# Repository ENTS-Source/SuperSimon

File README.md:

# ENTS "Simon Says" game

A two player version of the popular Simon Says game, with a fifth button.

## Pi Zero (2W) setup

1. Install Raspbian per normal
2. Enable SSH and WiFi to make configuration/development easier
3. `sudo apt update`
4. `sudo apt upgrade`
5. `sudo apt install python3-pgzero` (should already be installed)
6. Turn volume up on the Raspberry Pi and output device (speakers/monitor)
7. `git clone https://github.com/ENTS-Source/SuperSimon.git`
8. `cd SuperSimon`
9. `pgzrun simon.py` (to verify it works)

## Credits

Audio files are generated by ChatGPT under CC0 1.0

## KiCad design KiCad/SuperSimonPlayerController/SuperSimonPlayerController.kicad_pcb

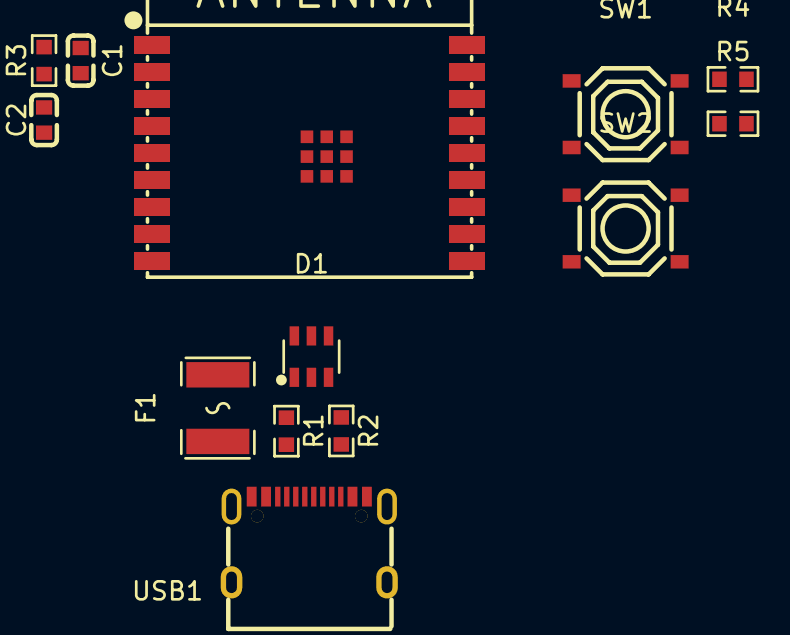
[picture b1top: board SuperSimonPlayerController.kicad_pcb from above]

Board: 2 copper layers, 13 parts (0 on the bottom side), 13 nets, no tracks yet.

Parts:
C1, C2: CL10A226MQ8NRNC; C0603
D1: USBLC6-2SC6; SOT-23-6_L2.9-W1.6-P0.95-LS2.8-BL
F1: BSMD1812-300-16V; F1812
R1, R2, R3, R4, R5: 0603WAF5101T5E; R0603
SW1, SW2: TS-1187A-B-A-B; SW-SMD_4P-L5.1-W5.1-P3.70-LS6.5-TL_H1.5
U1: ESP32-C3-WROOM-02-N4(4MB); BULETM-SMD_ESPRESSIF_ESP32-C3-WROOM-02-N4-4MB
USB1: TYPE-C 16PIN 2MD(073); USB-C-SMD_TYPE-C-6PIN-2MD-073

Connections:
/ESP32-C3-WROOM-02-N4/3Vin: C1.1, R3.2, R4.2, R5.2, U1.1 (3V3)
/ESP32-C3-WROOM-02-N4/D0/A0: R5.1, U1.16 (IO2)
/ESP32-C3-WROOM-02-N4/D8/SCK: R4.1, U1.7 (IO8)
/ESP32-C3-WROOM-02-N4/D9/MISO: SW2.2, U1.8 (IO9)
/ESP32-C3-WROOM-02-N4/ENABLE: C2.1, R3.1, SW1.2, U1.2 (EN)
/ESP32-C3-WROOM-02-N4/GND: C1.2, C2.2, SW1.3, SW2.3, U1.9 (GND), U1.19 (EP)
/USB-C/5VBUS: D1.5, F1.2
/USB-C/D+: D1.1, D1.6, USB1.6 (DP1), USB1.8 (DP2)
/USB-C/D-: D1.3, D1.4, USB1.5 (DN2), USB1.7 (DN1)
/USB-C/GND: D1.2, R1.1, R2.1, USB1.1 (GND), USB1.12 (GND)
/USB-C/UNPROTECTED5VBUS: F1.1, USB1.2 (VBUS), USB1.11 (VBUS)
unnamed: R1.2, USB1.4 (CC1)
unnamed: R2.2, USB1.10 (CC2)

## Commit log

2015-07-01 Change direction of repository; Add protocol specification (v1.0)
2015-07-01 Fix formatting of protocol
2015-07-04 Add note about 9600/8N1
2015-07-04 Add some notes
2015-07-05 Initial hardcoded UI for demonstration
2015-07-05 Improve UI slightly
2015-07-05 Add start of emulation code
2015-07-05 UI for emulator - no logic yet
2015-07-05 Add note about endianness for length of payload
2015-07-05 Add start of emulated protocol
2015-07-05 Add Echo command as command ID 1111 0000 (240)
2015-07-05 Add implementation of each command - no game pad function yet
2015-07-06 Full emulation of protocol
2015-07-06 Add outbound serial logging to emulator
2015-07-06 Add imports to debug protocol file for reference
2015-07-06 Use hexadecimal in protocol specs; Fix 'start game' step of game sequence incorrectly saying it uses an address; Minor touchups to document
2015-07-06 Fix emulator to use proper start game command specification
2015-07-06 Fix debug function for start game
2015-07-06 Minor emulator code cleanup
2015-07-06 Move emulated commands to a shared file to reduce file explosion
2015-07-06 Add some somewhat helpful debugging utilities
2015-07-06 Fix emulator's echo command to actually respond correctly
2015-07-06 Make Teensy code compile for emulation
2015-07-06 Code cleanup in emulator
2015-07-07 Update ENTS branding for Python UI
2015-07-07 Demonstrate a more organized UI
2015-07-07 Uncomment re-render in loop for performance testing
2015-07-08 Add magic value documentation
2015-07-08 Update debugging code and emulator to handle magic sequence
2015-07-08 Add 'end game now' (0x0A) to protocol. Not implemented in emulator yet; Also add information about magic sequence.
2015-07-08 Minor updates to protocol documentation
2015-07-09 Add information about timing
2015-07-09 Fix emulator for a few minor protocol things
2015-07-09 Populate README.md
2015-07-09 Add some information about timings to protocol
2015-07-09 Start of game code - includes start of an initial discover sequence
2015-07-09 Document joining a little bit better
2015-07-09 Start of new rendering code
2015-07-09 Cleanup of general code base
2015-07-09 Don't check joins at startup
2015-07-10 Define color depth for pygame window
2015-07-10 Increase some time limits to 150ms. See changes for info
2015-07-11 Add basic player rendering
2015-07-11 Attempt at some pre-game logic; Committing untested to fix performance
2015-07-11 Result of failed performance improvements (selective rendering didn't work)
2015-07-11 Attempt at improving render code. Leaderboard rendering decreased from >500ms to at most 218ms in testing
2015-07-11 Add player rendering code, mostly untested. Performance is ~250ms overall average game loop time, 750ms maximum
2015-07-12 Remove debug code
2015-07-12 Remove unused file
2015-07-12 Start of gameplay - missing game over state, forced game over, and ranking
2015-07-12 Make sure the proper game sequence makes it to the player
2015-07-12 Remove debugging lines
2015-07-12 Add game over state
2015-07-12 Decrease game over time from 15s to 10s
2015-07-12 Re-fix skipping of rounds with an ugly hack
2015-07-12 Minor code cleanup
2015-07-13 Implement response magic value; Update communications to support a proper order of operations
2015-07-13 Clean up game request code just a little bit
2015-07-13 Re-comment the timing code on the read byte function
2015-07-13 Minor updates and improvements
2015-07-15 Remove now-obsolete debug code
2015-07-15 Fix various bugs
2015-07-15 Decrease time spent waiting for players
2015-07-15 Add basic scoring
2015-07-15 Remove example database file
2015-07-16 Minor bugfixes to deal with multiplayer setups
2015-07-17 Last minute fixes
2015-07-20 Minor UI improvements and game fixes
2015-07-24 PEP8 compliance
2015-07-27 Template JavaFX project
2015-07-27 Fix up pom
2015-07-27 Start of UI testing
2015-07-28 Increase minimum screen size
2015-07-28 Don't use deprecated variables in pom.xml
2015-07-28 Add some debugging lines
2015-08-03 Some UI and lots of database
2015-08-03 Database init
2015-08-03 Untested partial completion of IO code
2015-08-03 More network IO stuff; Some cleanup
2015-08-03 Comments and temporary code for debugging
2015-08-04 Tested IO code for echo command
2015-08-04 Reduce protocol search area to decrease time spent loading
2015-08-04 Reorganization and some cleanup of IO code
2015-08-04 Misc. cleanup
2015-08-04 Template for configuration stuff
2015-08-08 Add template for web UI
2015-08-08 Database and some UI configuration implementation
2015-08-08 Updates to theme files to remove excess whitespace
2015-08-09 Start of some actual player handling code
2015-08-09 Handle commands that do not send a return address
2015-08-09 Document the lack of address on SimonCommand a bit better
2015-08-09 Copy web information to target; Include a 'dist' output folder
2015-08-09 Documentation
2015-08-09 Correctly set up the session manager for the game
2015-08-10 Fix traffic flow for multi-session environments
2015-08-10 Hide window on close
2015-08-10 Add player count to screen in a visible location
2015-08-10 Start use of stylesheets
2016-07-15 Added a shutdown button
2016-07-15 Fix spelling mistakes
2018-07-15 First round of changes for 2018 refresh
2018-07-15 Add to ignore file
2018-07-15 Move participants up a bit
2018-07-15 Accept ALT+F4
2018-07-15 Use escape to exit
2018-07-15 Use the correct equals
2018-07-15 Fit for a 720p screen
2018-07-15 Drop thin font down a bit
2018-07-15 Include last known Teensy code
2018-07-15 Include a future code for "Reset state"
2018-07-15 Hide mouse cursor
2018-07-16 Add missing command definitions
2018-07-21 Add support for logging to matrix
    This is done in a non-fatal way so if no homeserver is available, we just won't log anything
2018-07-30 Ensure sequences don't contain duplicate buttons
2022-07-13 Python 3.7 support?
2022-07-14 Remove GPIO stuff
2022-07-14 Remove Matrix stuff
2022-07-16 debugging
2022-07-17 Use byte strings and more pyserial args
2022-07-17 Fix byte string handling
2022-07-17 Remove excess debugging
2025-03-07 K-Days 2025 Initial Commit
    Setup KiCad directory
    Made ENTS Drawing Sheet
    Created Player Controller Project
    Created Environment Variable ENTS_SUPERSIMON_GITHUB_PATH
    Created parts libraries
    Made USB schematic page
2025-03-08 Update README.md with KiCad setup instructions.
2025-03-08 Added tech notes to USB schematic
2025-03-08 Swapped to esp32-c3 with castallated pads, added some passives, created schematic sheet for the esp32
2025-03-09 made 3D models use relative paths
2025-03-09 Added switches and boot-strapping pull-ups to esp32-c3
2025-06-22 reset and switch to pygame zero
2025-06-22 fix window
2025-06-22 ok, move it into the main file
2025-06-22 import
2025-06-22 blit logo
2025-06-22 start with game modes
2025-06-22 python
2025-06-22 x/y?
2025-06-22 fix design
2025-06-22 Test music mode
2025-06-22 Apply random detuning
2025-06-22 Shift up an octave
2025-06-22 Add some background music
2025-06-22 move music to correct directory
2025-06-22 switch to mp3?
2025-06-22 adjust volume
2025-06-22 credit the robots
2025-06-23 Use low sounds for now
2025-06-23 We'll do the high tones for now
2025-06-23 synthesized square wave piano
2025-06-23 try some generated DDR sounds
2025-06-23 Add simon sounds
2025-06-23 Add some sound effects
2025-06-28 Reorganize a bit
2025-06-29 First cut of the normal game mode
2025-06-29 fix database
2025-06-29 Actually start the game
2025-06-29 Track state a bit better
2025-06-29 debug
2025-06-29 Maybe bind differently?
2025-06-29 try just schedule
2025-06-29 fix according to chatgpt
2025-06-29 fix class vs instance
2025-06-29 refactor per gpt
2025-06-29 fix?
2025-06-29 Fix button state
2025-06-29 fix DB
2025-06-30 End games when they're done
2025-06-30 Actually continue the game properly
2025-06-30 too many schedules?
2025-06-30 full commit
2025-06-30 instance vars
2025-07-06 Start supporting GPIO
2025-07-06 add debugging script
2025-07-06 never exit
2025-07-06 less never
2025-07-06 even less never
2025-07-06 fstring correctly
2025-07-07 for debugging
2025-07-07 check correctly
2025-07-07 adjust timing
2025-07-07 Show sequence button, not index button
2025-07-07 Clear player button state
2025-07-07 game over visuals
2025-07-07 Fix horrible noises
2025-07-07 Update game over sound
2025-07-07 rename for easier tab complete
2025-07-07 add player 2
2025-07-13 Set up player 2 properly in the game
2025-07-13 also remove hacks
2025-07-13 up game over time (for scores later)
2025-07-13 start testing
2025-07-13 adjust positioning
2025-07-13 sizing
2025-07-13 Adjust sizing
2025-07-13 Adjust window size
2025-07-13 wrong size
2025-07-13 Start adding details
2025-07-13 add detail
2025-07-13 details
2025-07-13 add player boxes
2025-07-13 detail
